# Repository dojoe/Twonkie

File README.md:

# Twonkie - a USB-PD sniffer based on Google's [Twinkie](https://www.chromium.org/chromium-os/developer-library/guides/hardware-schematics/twinkie/)

Twonkie is a USB-PD sniffer/injector/sink based on a Google project called Twinkie, re-engineered to be made in one-off quantities by mere mortals.

Twinkie is a great and pretty low-cost solution, and it's open-source so anyone could make their own, but unfortunately the Twinkie design uses a six-layer PCB and all BGA/wafer-scale parts - both of which are usually unavailable to the humble hobbyist.

So I designed the Twonkie, a slightly wonky sibling of Twinkie. It uses a four-layer PCB that can be manufactured cheaply by lots of services like OSHPark, and it makes a point to use only leaded parts for easier soldering (though the main microcontroller can optionally be QFN too via a dual footprint). The most difficult parts are likely the passives which are all 0402, and the USB-C connectors which are used in an unconventional way by misusing 90° upright connectors as 1.6mm straddle mounts (living up to the concept of being wonky).

## What does it look like?

Lookie here!

The PCB is exactly 1 inch squared, so $10 will get you three at OSHPark. In fact, let me take care of that for you:

<a href="https://oshpark.com/shared_projects/pj6N7ZkZ"></img></a>

_(Disclaimer: I am not affiliated with OSHPark, I just love their service to bits and they've been super helpful chaps time and time again.)_

The v1.0 and v2.0 Gerbers in this repo no longer need the botch wires around Q4 either, I'll update the photo as soon as I get the next board revision back.

## What's changed compared to the original Twinkie?

 * A bootloader button in addition to the USB_ID pin based bootloader selection.
 * Uses the INA237 part which supports the higher supply voltages of USB-PD Extended Power Range (EPR)
 * The microcontroller pins are rearranged for easier routing, so you'll need a different firmware. Binaries are provided and the firmware is easy to build from source.
 * The USB-C connectors are attached in a hair-raising straddle mount configuration. The way they're soldered to the PCB makes them rock solid though, maybe even more solid than the original Twinkie, and they transfer TB3 20Gbit/s lanes just fine.

## I see there's a v2.0 now - what's different?

The 2.0 version uses a different voltage/current monitor chip compared to Twonkie v1.0, the [INA237](ref/ina237.pdf), which supports higher bus voltages and therefore makes the Twonkie hardware ready for Extended Power Range (EPR). The INA260 used by Twonkie v1.0 (and the INA231 used by Twinkie) will take damage if subjected to the up to 48V specified by EPR.

## Sweet! How do I build my own?

I'm glad you asked! Get the board made via the OSH Park link above, or supply the v2.0 Gerbers in this repository to a PCB fab of your choice, get the parts from Digikey or Mouser or what have you, and follow the [Assembly instructions](hw/README.md) to build the device. I recommend ordering a few extra parts: Get one more of each Type-C connector since you're going to modify them in ways that might end up with a broken connector, and generously round up the number of 0402 passives since you're going to drop some of them and you will _never_ find them again :)

For the firmware, there are [Instructions for building and flashing](fw/README.md) in the [fw](fw) directory.

## None of the parts are available 😭 What do I do?

Here are some ideas about replacements for some parts that are most likely to be unavailable. None of these have been tested so you're on your own!

 * **INA237:** The INA237 is part of a device family and has two siblings with higher specs that TI claims are drop-in replacements: INA228 and INA238.
 * **STM32F072CB:** For one, the Twonkie has a dual footprint that will fit both the TQFP and QFN variants, i.e. the STM32F072CBT and STM32F072CBU. And if you are willing to sacrifice the PD sink functionaliy and only need the sniffer functionality you could also try the variants with 64k flash instead of 128k (STM32F072C8*) and only flash the first half of the firmware binary. Other device families than the F072 would require extensive firmware changes so I can't recommend that.
 * **USB-C plug / receptacle:** These might be a little trickier. Basically you need one that's meant for being mounted standing up on a board, has all USB-C pins wired out to L shaped pins and doesn't have any metal mounting prongs protruding into the board plane (or if it has you'll have to cut them off).

## I am a noob trying to solder and replicate the Twonkie. Got any beginner tips?

The KiCad schematic file contains the vendor part numbers and DigiKey order numbers for each part designator, and I exported the full list into a .csv file too - those are commonly called "Bill of materials" or BOM for short, and [this is the one for Twonkie 2.0](hw/v2.0/twonkie.bom.csv). You should be able to punch those part numbers into a parts supplier of your choice (I usually use [DigiKey](https://digikey.com/) but there are plenty others) to find the parts you need. If they have parts in stock they'll happily sell you small quantities, though at an increased price. Take care to order more of most parts than you need - especially the tiny passives (resistors, capacitors...) are easy to lose during assembly.

As for reading the schematic, it probably helps to have some familiarity with [USB-PD](https://www.usb.org/document-library/usb-power-delivery) and the [original project description](https://www.chromium.org/chromium-os/developer-library/guides/hardware-schematics/twinkie/), and then read up on the [device datasheets](ref/) to understand which part does what.

Having said all that, please be warned that the Twonkie is not exactly a noob project - unless you're already familiar with hand-soldering fine pitch SMT parts you may be in for a frustrating experience. Don't let that keep you from trying, but you should know what you're signing up for :)

# TODOs

 * [ ] Get Twinkie support upstreamed in sigrok/PulseView
 * [ ] v2.0 photos

# Similar projects

 * As luck would have it, [Greg Davill](https://github.com/gregdavill) started a project with the exact same goal at a very similar time, so there's now two of us :) https://github.com/gregdavill/PD-sniffer
 * [XenGi](https://github.com/XenGi) built a version of Twonkie v2.0 which uses a 0.8mm PCB and industry-standard straddle mount USB-C connectors. After [a bit of deliberation](https://github.com/dojoe/Twonkie/issues/10) I decided to stick with the 1.6mm PCB for stability and availability reasons but if you prefer a less haxxy way of attaching the connectors (and a 3D printed case!) feel free to check out his repo: https://gitlab.com/XenGi/Twonkie
   
# Licenses

## Hardware (as found in the `hw` subdirectory)

<p xmlns:cc="http://creativecommons.org/ns#" xmlns:dct="http://purl.org/dc/terms/">The hardware design of <a property="dct:title" rel="cc:attributionURL" href="https://github.com/dojoe/Twonkie">Twonkie</a> by <a rel="cc:attributionURL dct:creator" property="cc:attributionName" href="https://github.com/dojoe">Joachim "dojoe" Fenkes</a> is licensed under <a href="http://creativecommons.org/licenses/by/4.0/" target="_blank" rel="license noopener noreferrer" style="display:inline-block;">CC BY 4.0</a></p>

## Firmware (as found in the `fw` subdirectory)

The source code for the Twonkie's firmware is licensed under the 3-clause BSD license, see [its LICENSE file](fw/LICENSE).

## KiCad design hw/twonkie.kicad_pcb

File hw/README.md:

# Before you begin

## Recommended tools (apart from the usual)

The board is too tiny to stay put from its own weight so you'll need a proper vise. "Third Hand"s are no good for this since they can't clamp small boards properly and aren't stable enough. I recommend a StickVise or similar.

A knife with a straight, strong blade.

Non-serrated pliers.

You can solder everything using a smallish chisel tip and you'll be fine.
For enhanced comfort, a fine angled tip makes the passives much easier. I used a TS80-J02 with great success.

Gel flux. Liquid flux evaporates too quickly for my taste. I use Edsyn FL-22 for everything but there's plenty other good stuff out there too.

A watchmaker's loupe, more for inspection than for the actual soldering. Of all the tools I acquired last year, this super cheap 7x loupe made the biggest difference and it's never leaving my workbench again. Have a strong light (such as a phone camera LED) at the ready for inspection too, there's no such thing as "too much light".

## General tips

 * Keep both the schematics and the board file open while you build, you'll likely want to refer back to them more often than not.

 * I wholeheartedly recommend this thread by [@thingskatedid](https://twitter.com/thingskatedid): https://twitter.com/thingskatedid/status/1348234262886039558

 * **The passives are indistinguishable once taken out of their tapes!**
   * Always work with a single value at a time
   * Only remove as many components from the tape as you need right now
   * Immediately put the tape back into the pouch it came in, as that's where the value is noted - or write the value onto the tape.

 * For each group of passives below, it saves time to batch up different types of operations: First put a small solder blob on one pad of each site, then tack down each component, then solder the other side for all components in a row.

 * If the solder joints on nearby passives blob together a lot, use some flux and a little less solder. It's also a good idea to make a final flux pass across the finished passives just like you would be drag soldering a leaded part, it makes the solder joints look a lot nicer.

# Assembly instructions

These instructions are optimized for hand assembly; the components are grouped in a way that if you follow the groups in order you should never have one component in the way of soldering another. Within a given group the order does not matter; I recommend doing all components of one value before moving on to the next value.

The overall order of assembly is:
 1. Back side components
 2. Front side components
 3. Basic connectivity/bootloader test
 4. USB-C connectors

## Part 1: Back side

We start on the back side because that's where the STM32 sits which is the most daunting to solder, and because the components on that side are generally flatter so if you _have_ to solder without a vise they won't make the board as wobbly when you do the front side.

If your STM32 is a QFN part, take extra care to inspect its solder joints after you put it down. Once the board is fully populated any bad solder joints here will be hard to fix.

| Group | Components          | Value        |
|-------|---------------------|--------------|
| 1     | U4                  | STM32        |
| 2     | R3                  | 400          |
|       | R2, R5              | 620          |
| 3     | DS1                 | LED          |
| 4     | C3, C8              | 100n         |
|       | C7                  | 4.7µ         |
|       | C1                  | 1µ           |
|       | R4                  | 400          |
|       | FB1                 | Ferrite Bead |
| 5     | D1, U1, U3, Q4, R28 |              |

## Part 2: Front side

| Group | Components                 | Value         |
|-------|----------------------------|---------------|
| 6     | Q1, Q2, Q3                 | NFET          |
| 8     | R9, R17, R25, R26          | 4k75          |
|       | R10, R18                   | 1k            |
|       | R11, R19                   | 12k1          |
|       | R12, R20                   | 5k11          |
|       | R6, R7                     | 400           |
|       | R15, R23, R24              | 100           |
|       | R14, R22                   | 200           |
| 9     | R1, R8, R13, R16, R21, R27 | 35k7          |
| 10    | C2                         | 4u7           |
|       | C4, C9                     | 100n          |
|       | C5                         | 1u            |
|       | C6                         | 10n           |
| 11    | FB2                        | Ferrite Bead  |
| 12    | DS2, U5, U2, J3, SW1, R29  |               |

## Part 3: Basic connectivity / bootloader test

This step is done on the not-quite-finished Twonkie because if anything isn't right the board is much easier to hold in the vise without two USB-C connector sticking out.

1. Double check all components:
   * Are all ICs oriented the right way?
   * Did you miss any solder joints?
   * Do you see any obvious solder bridges?
2. Measure resistance between the 3V3 rail and GND, this is easiest at the output side of U3.
   Kiloohms are good, Ohms are an indication of a short somewhere.
3. Do the same on the input side of U3.
4. Hold down the bootloader switch and plug the dongle in via the Micro-B connector.
   It should now enumerate as the bootloader (VID 0x0483, PID 0xDF11, "STM32 BOOTLOADER")
5. Flash the firmware via the bootloader, then unplug and plug back in to boot the Twonkie firmware.
   * Check out the [Firmware README](../fw/README.md) for building and flashing instructions.
6. You can test the LED using the serial shell:
   * `tw sink` puts the device into sink mode where the firmware doesn't keep overwriting the LED state.
     You may need to reconnect the shell after this.
   * `gpioset LED_B_L 0` turns the blue LED on, `gpioset LED_B_L 1` turns it off.
   * Same for `LED_R_L` and `LED_G_L`
7. Check I2C connectivity to the two INA260 monitors:
   * `ina 0` attempts to access U1, `ina 1` does so for U2

That's all we can test for now, let's finish the board next.

## Part 4: USB-C connectors

The USB-C connectors are used in an unorthodox way: Straddle mount USB-C connectors for 1.6mm boards don't exist, so we take connectors meant for right-angle surface mounting and modify them into our own custom straddle mount configuration. With those modifications the solder connections work really well, and we achieve mechanical stability by soldering the connector shields to the board all around.

We start out with the unmodified connector. This is the receptacle but the steps for the plug are identical.

First, the mounting legs have to get out of the way. Grab them with your pliers and bend them back and forth until they break off.

Next up, the locating pegs have to go too. Cut them off close to the base.

Now comes the tricky part: We have to bend the pins of the connector slightly inwards so they touch the board edge at an angle, but not so much that they don't reach the board edge or break off. The photos should give you an idea of how far to bend them.

Start by sliding the knife under roughly a quarter to half the pins on one side, and gently bend them inwards. Bending only part of the pins at once requires less force and therefore allows for better control. Take care to **rotate** the knife blade around the long axis, as opposed to using it as a lever, so that all pins receive equal force and bend the same way.

Move along the row of pins, bending groups of pins inwards until the entire row is bent.

Repeat the same process on the other side; the end result should look something like this:

Now you can slide the connector into its place on the PCB. The PCB is designed such that the shell sits inside the PCB with a slight press fit. If you feel it's jammed in there too tightly you can simply sand off a little bit of the PCB, but sand off only very little and try to sand off both sides equally to maintain pin alignment.

Push the connector all the way towards the board edge and adjust its position until it sits exactly centered and in line with the board:

The pins on both sides should now align with the pads and touch the corner of the board edge. If there's a tiny gap that's no problem, the solder will bridge that. Larger gaps need to be fixed by adjusting the connector's position or bending the pins to compensate.

Once you're satisfied with the connector, tack down _one_ pin on one board side, double check that everything still looks good, then tack down _one_ pin on the opposite side. Triple check that everything still looks good, then you can drag solder all the pins into place.

When the pins have all been soldered, inspect them for missing connections or solder bridges and correct any that come up.

Finally you can solder down the shells: Using a soldering iron that can pump out a bit of heat (TS-80 is good, TS-100 is better, a powerful temperature controlled soldering station is best), first just pre-heat the shell for a bit, then add some solder and make sure it wets along the entire length of the neighboring pad. Then you can start heating the pad too and add loads of solder to make a solid connection. Do this on all four mounting pads and the connector won't go anywhere.

## Part 5: Enjoy!

And that's it! Clean your board with isopropanol and have fun with your new PD sniffer!

### Test 1: Sniff some power supply traffic

For starters, you can open a shell, type `tw trace on` and plug Twonkie in between a PD power supply and sink to watch them negotiate a power contract.

A very good test for many of the board devices is to do this in all four possible combinations of input and output plug orientation. The supply and sink should be able to negotiate a contract in all orientations, and Twonkie should be able to trace all of this. If some orientations don't work, check the solder joints on the USB-C connectors for bridges or opens - especially opens can be very sneaky with the haxxy edge mount we're using. If the connectors look alright, check the board devices next - especially the resistor banks and transistors are likely culprits since they directly interact with the USB-C control channels.

### Test 2: Twonkie as sink

The second test would be to attach only a power supply to Twonkie, with no sink at the other end, and type `tw sink` at the shell to put Twonkie into sink mode. (You may have to reconnect to the shell since Twonkie reboots into a different firmware.) Once in sink mode you can type `tw vbus` to watch what voltage the supply provides, and `pd 0 dev X` will limit the negotiated voltage to a maximum of `X` volts, so you can step through various supply voltages and watch them change. Test this in either plug orientation too; if you're having problems here you should double check the resistor banks on the control channels.

To go from sink mode back to sniffer mode you can type `reboot` at the shell.

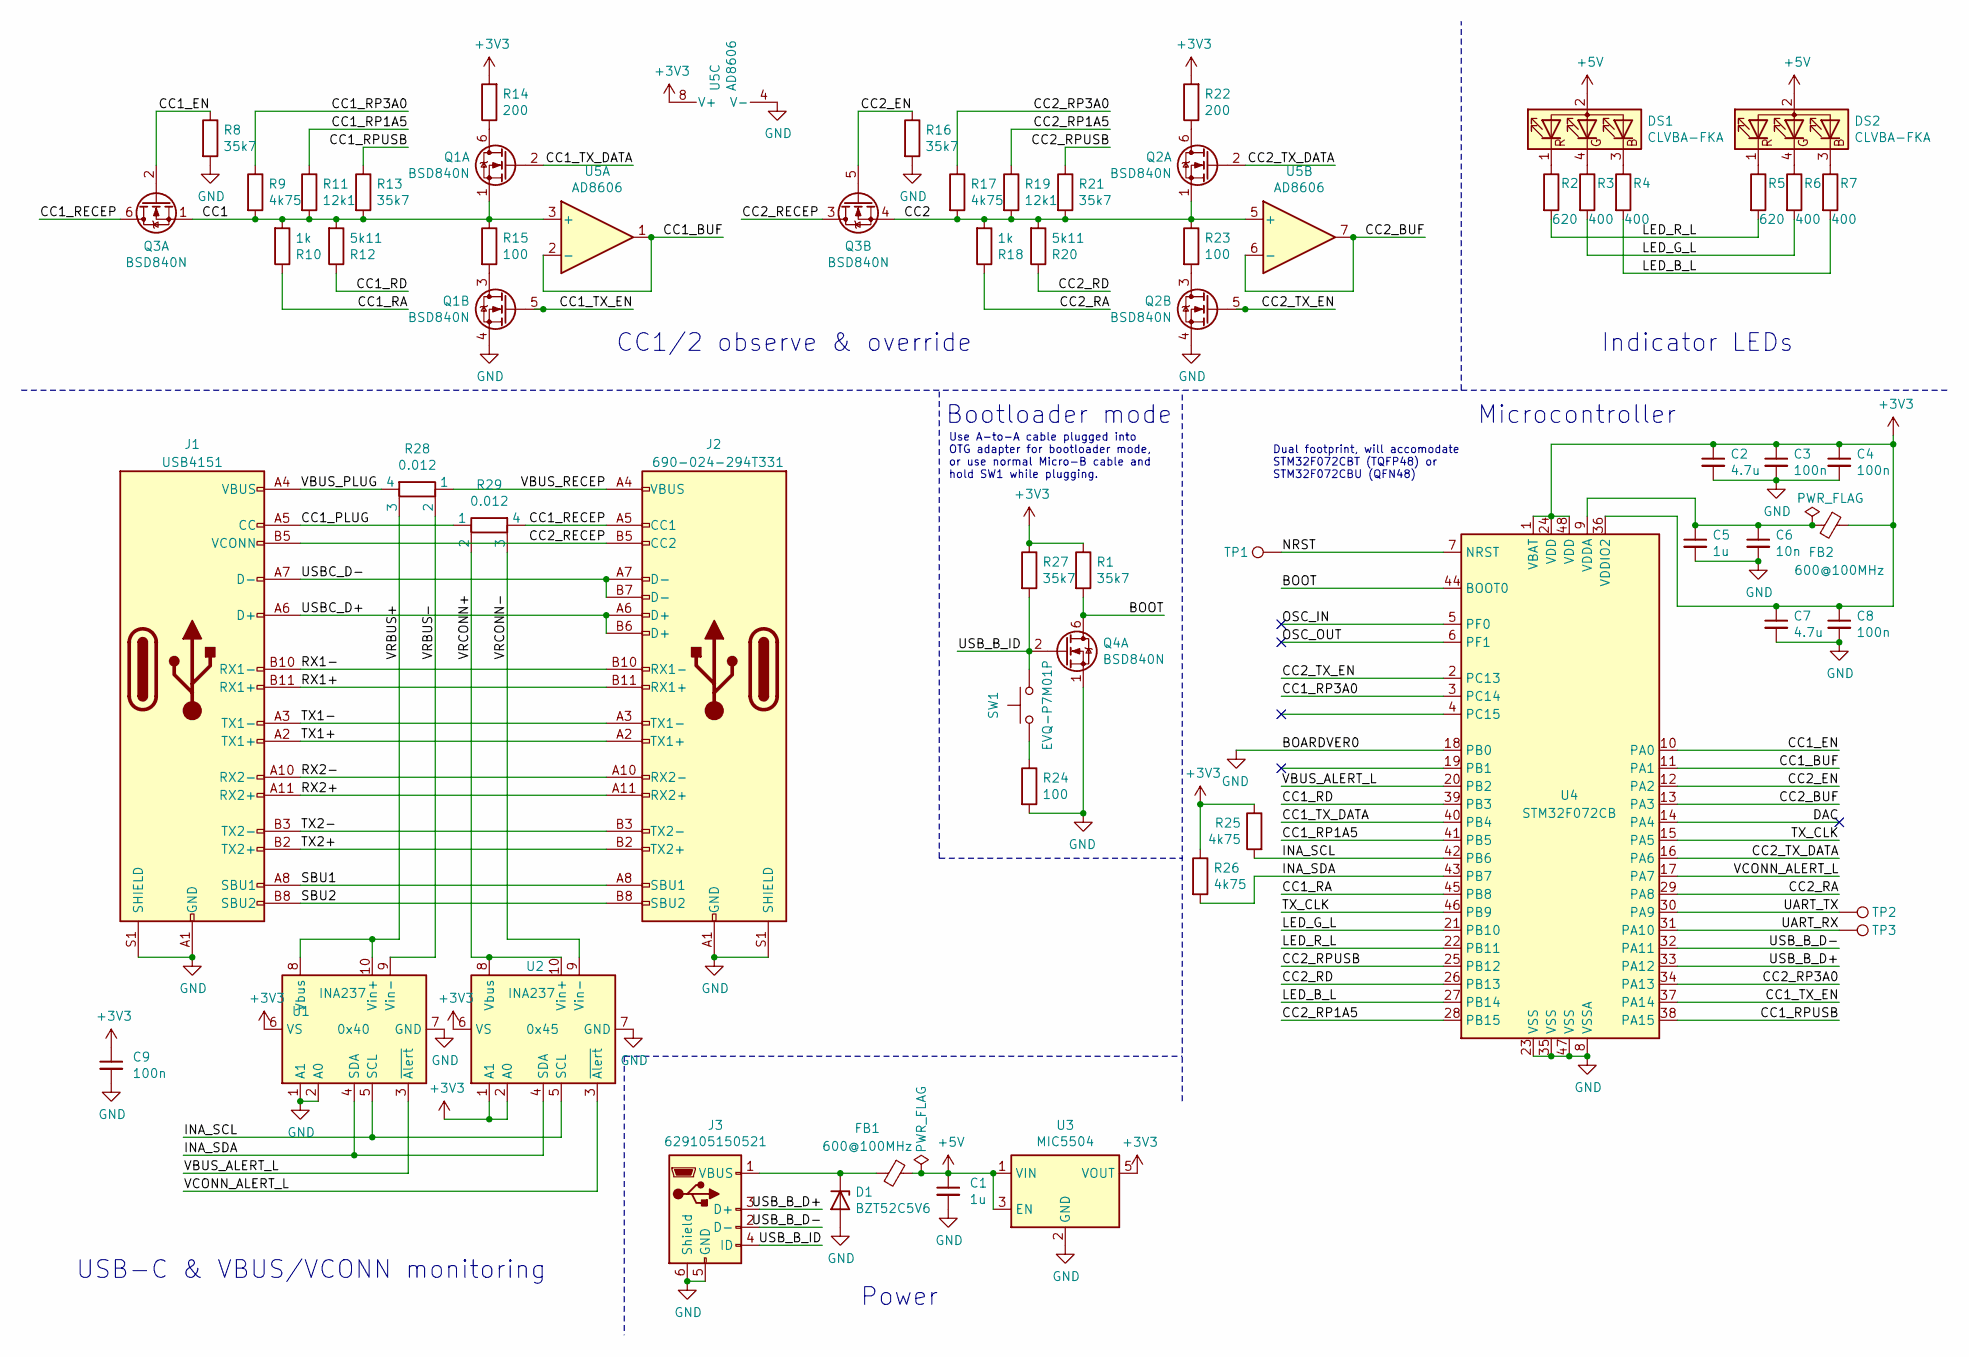
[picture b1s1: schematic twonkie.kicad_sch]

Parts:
C1, C5: 1u; C_0402_1005Metric_Pad0.74x0.62mm_HandSolder; Mfg P/N CL05A105MQ5NNNC; DigiKey P/N 1276-1235-1-ND
C2, C7: 4.7u; C_0402_1005Metric_Pad0.74x0.62mm_HandSolder; Mfg P/N CL05A475KQ5NRNC; DigiKey P/N 1276-1481-1-ND
C3, C4, C8, C9: 100n; C_0402_1005Metric_Pad0.74x0.62mm_HandSolder; Mfg P/N CL05B104KA5NNNC; DigiKey P/N 1276-6720-1-ND
C6: 10n; C_0402_1005Metric_Pad0.74x0.62mm_HandSolder; Mfg P/N CL05B103KB5NNNC; DigiKey P/N 1276-1028-1-ND
D1: BZT52C5V6; D_SOD-123; Mfg P/N BZT52C5V6-13-F; DigiKey P/N BZT52C5V6-13-FDICT-ND
DS1, DS2: CLVBA-FKA; LED_Cree-PLCC4_3.2x2.8mm_CCW; Mfg P/N CLVBA-FKA-CAEDH8BBB7A363; DigiKey P/N CLVBA-FKA-CAEDH8BBB7A363CT-ND
FB1, FB2: 600@100MHz; L_0402_1005Metric_Pad0.77x0.64mm_HandSolder; Mfg P/N BLM15AG601SN1D; DigiKey P/N 490-1006-1-ND
J1: USB4151; GCT_USB4151_EdgeMount; Mfg P/N USB4151-GF-C; DigiKey P/N 2073-USB4151-GF-CCT-ND
J2: 690-024-294T331; EDAC_690-024-294T331_EdgeMount; Mfg P/N USB4070-30-C; DigiKey P/N 2073-USB4070-30-CCT-ND
J3: 629105150521; USB_Micro-B_Wuerth_629105150521_HandSolder; Mfg P/N 629105150521; DigiKey P/N 732-5960-1-ND
Q1, Q2, Q3, Q4: BSD840N; SOT-363_SC-70-6; Mfg P/N BSD840NH6327XTSA1; DigiKey P/N BSD840NH6327XTSA1CT-ND
R1, R8, R13, R16, R21, R27: 35k7; R_0402_1005Metric_Pad0.72x0.64mm_HandSolder; Mfg P/N RC0402FR-0735K7L
R2, R5: 620; R_0402_1005Metric_Pad0.72x0.64mm_HandSolder; Mfg P/N RC0402FR-07620RL
R3, R4, R6, R7: 400; R_0402_1005Metric_Pad0.72x0.64mm_HandSolder; Mfg P/N RC0402FR-07402RL
R9, R17, R25, R26: 4k75; R_0402_1005Metric_Pad0.72x0.64mm_HandSolder; Mfg P/N RC0402FR-074K75L
R10, R18: 1k; R_0402_1005Metric_Pad0.72x0.64mm_HandSolder; Mfg P/N RC0402FR-071KL
R11, R19: 12k1; R_0402_1005Metric_Pad0.72x0.64mm_HandSolder; Mfg P/N RC0402FR-0712K1L
R12, R20: 5k11; R_0402_1005Metric_Pad0.72x0.64mm_HandSolder; Mfg P/N RC0402FR-075K11L
R14, R22: 200; R_0402_1005Metric_Pad0.72x0.64mm_HandSolder; Mfg P/N RC0402FR-07200RL
R15, R23, R24: 100; R_0402_1005Metric_Pad0.72x0.64mm_HandSolder; Mfg P/N RC0402FR-07100RL
R28, R29: 0.012; R_Shunt_Ohmite_LVK12; DigiKey P/N LVK12R012FERCT-ND
SW1: EVQ-P7M01P; SW_SPST_EVQP7C; Mfg P/N EVQ-P7M01P; DigiKey P/N P16770CT-ND
TP1, TP2, TP3: TestPoint; TestPoint_Pad_D1.0mm
U1, U2: INA237; VSSOP-10_3x3mm_P0.5mm; Mfg P/N INA237AIDGSR; DigiKey P/N 296-INA237AIDGSRCT-ND
U3: MIC5504; SOT-23-5_HandSoldering; Mfg P/N MIC5504-3.3YM5-TR; DigiKey P/N 576-4764-1-ND
U4: STM32F072CB; LQFP-48_7x7mm_P0.5mm-QFN48-Frankenstein; Mfg P/N STM32F072CBT; DigiKey P/N 497-18747-1-ND
U5: AD8606; MSOP-8_3x3mm_P0.65mm; Mfg P/N AD8606ARMZ-R7; DigiKey P/N 505-AD8606ARMZ-R7CT-ND

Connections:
+3V3: C2.1, C3.1, C4.1, C7.1, C8.1, C9.1, FB2.1, R1.1, R14.2, R22.2, R25.1, R26.1, R27.1, U1.6 (VS), U2.1 (A1), U2.2 (A0), U2.6 (VS), U3.5 (VOUT), U4.1 (VBAT), U4.24 (VDD), U4.36 (VDDIO2), U4.48 (VDD), U5.8 (V+)
+5V: C1.1, DS1.2 (A), DS2.2 (A), FB1.1, U3.1 (VIN), U3.3 (EN)
/BOOT: Q4.6 (D), R1.2, U4.44 (BOOT0)
/CC1: Q1.1 (S), Q3.1 (S), R9.2, R10.2, R11.2, R12.2, R13.2, R15.1, U5.3 (+)
/CC1_BUF: U4.11 (PA1), U5.1, U5.2 (-)
/CC1_EN: Q3.2 (G), R8.1, U4.10 (PA0)
/CC1_PLUG: J1.A5 (CC), R29.1
/CC1_RA: R10.1, U4.45 (PB8)
/CC1_RD: R12.1, U4.39 (PB3)
/CC1_RECEP: J2.A5 (CC1), Q3.6 (D), R29.4
/CC1_RP1A5: R11.1, U4.41 (PB5)
/CC1_RP3A0: R9.1, U4.3 (PC14)
/CC1_RPUSB: R13.1, U4.38 (PA15)
/CC1_TX_DATA: Q1.2 (G), U4.40 (PB4)
/CC1_TX_EN: Q1.5 (G), U4.37 (PA14)
/CC2: Q2.1 (S), Q3.4 (S), R17.2, R18.2, R19.2, R20.2, R21.2, R23.1, U5.5 (+)
/CC2_BUF: U4.13 (PA3), U5.6 (-), U5.7
/CC2_EN: Q3.5 (G), R16.1, U4.12 (PA2)
/CC2_RA: R18.1, U4.29 (PA8)
/CC2_RD: R20.1, U4.26 (PB13)
/CC2_RECEP: J1.B5 (VCONN), J2.B5 (CC2), Q3.3 (D)
/CC2_RP1A5: R19.1, U4.28 (PB15)
/CC2_RP3A0: R17.1, U4.34 (PA13)
/CC2_RPUSB: R21.1, U4.25 (PB12)
/CC2_TX_DATA: Q2.2 (G), U4.16 (PA6)
/CC2_TX_EN: Q2.5 (G), U4.2 (PC13)
/DAC: U4.14 (PA4)
/INA_SCL: R25.2, U1.5 (SCL), U2.5 (SCL), U4.42 (PB6)
/INA_SDA: R26.2, U1.4 (SDA), U2.4 (SDA), U4.43 (PB7)
/LED_B_L: R4.2, R7.2, U4.27 (PB14)
/LED_G_L: R3.2, R6.2, U4.21 (PB10)
/LED_R_L: R2.2, R5.2, U4.22 (PB11)
/NRST: TP1.1, U4.7 (NRST)
/OSC_IN: U4.5 (PF0)
/OSC_OUT: U4.6 (PF1)
/RX1+: J1.B11 (RX1+), J2.B11 (RX1+)
/RX1-: J1.B10 (RX1-), J2.B10 (RX1-)
/RX2+: J1.A11 (RX2+), J2.A11 (RX2+)
/RX2-: J1.A10 (RX2-), J2.A10 (RX2-)
/SBU1: J1.A8 (SBU1), J2.A8 (SBU1)
/SBU2: J1.B8 (SBU2), J2.B8 (SBU2)
/TX1+: J1.A2 (TX1+), J2.A2 (TX1+)
/TX1-: J1.A3 (TX1-), J2.A3 (TX1-)
/TX2+: J1.B2 (TX2+), J2.B2 (TX2+)
/TX2-: J1.B3 (TX2-), J2.B3 (TX2-)
/TX_CLK: U4.15 (PA5), U4.46 (PB9)
/UART_RX: TP3.1, U4.31 (PA10)
/UART_TX: TP2.1, U4.30 (PA9)
/USBC_D+: J1.A6 (D+), J2.A6 (D+), J2.B6 (D+)
/USBC_D-: J1.A7 (D-), J2.A7 (D-), J2.B7 (D-)
/USB_B_D+: J3.3 (D+), U4.33 (PA12)
/USB_B_D-: J3.2 (D-), U4.32 (PA11)
/USB_B_ID: J3.4 (ID), Q4.2 (G), R27.2, SW1.1
/VBUS_ALERT_L: U1.3 (~Alert), U4.20 (PB2)
/VBUS_PLUG: J1.A4 (VBUS), J1.A9 (VBUS), J1.B4 (VBUS), J1.B9 (VBUS), R28.4
/VBUS_RECEP: J2.A4 (VBUS), J2.A9 (VBUS), J2.B4 (VBUS), J2.B9 (VBUS), R28.1
/VCONN_ALERT_L: U2.3 (~Alert), U4.17 (PA7)
/VRBUS+: R28.3, U1.8 (Vbus), U1.10 (Vin+)
/VRBUS-: R28.2, U1.9 (Vin-)
/VRCONN+: R29.2, U2.8 (Vbus), U2.10 (Vin+)
/VRCONN-: R29.3, U2.9 (Vin-)
GND: C1.2, C2.2, C3.2, C4.2, C5.2, C6.2, C7.2, C8.2, C9.2, D1.2 (A), J1.A1 (GND), J1.A12 (GND), J1.B1 (GND), J1.B12 (GND), J1.S1 (SHIELD), J1.S2 (SHIELD), J1.S3 (SHIELD), J1.S4 (SHIELD), J1.S5 (SHIELD), J1.S6 (SHIELD), J2.A1 (GND), J2.A12 (GND), J2.B1 (GND), J2.B12 (GND), J2.S1 (SHIELD), J2.S2 (SHIELD), J2.S3 (SHIELD), J2.S4 (SHIELD), J2.S5 (SHIELD), J2.S6 (SHIELD), J2.S7 (SHIELD), J2.S8 (SHIELD), J3.5 (GND), J3.6 (Shield), Q1.4 (S), Q2.4 (S), Q4.1 (S), R8.2, R16.2, R24.2, U1.1 (A1), U1.2 (A0), U1.7 (GND), U2.7 (GND), U3.2 (GND), U4.8 (VSSA), U4.18 (PB0), U4.23 (VSS), U4.35 (VSS), U4.47 (VSS), U5.4 (V-)
unnamed: C5.1, C6.1, FB2.2, U4.9 (VDDA)
unnamed: D1.1 (K), FB1.2, J3.1 (VBUS)
unnamed: DS1.1 (RK), R2.1
unnamed: DS1.3 (BK), R4.1
unnamed: DS1.4 (GK), R3.1
unnamed: DS2.1 (RK), R5.1
unnamed: DS2.3 (BK), R7.1
unnamed: DS2.4 (GK), R6.1
unnamed: Q1.3 (D), R15.2
unnamed: Q1.6 (D), R14.1
unnamed: Q2.3 (D), R23.2
unnamed: Q2.6 (D), R22.1
unnamed: R24.1, SW1.2

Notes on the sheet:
Use A-to-A cable plugged into OTG adapter for bootloader mode, or use normal Micro-B cable and hold SW1 while plugging.
Dual footprint, will accomodate STM32F072CBT (TQFP48) or STM32F072CBU (QFN48)
Bootloader mode
Indicator LEDs
Power
CC1/2 observe & override
Microcontroller
USB-C & VBUS/VCONN monitoring

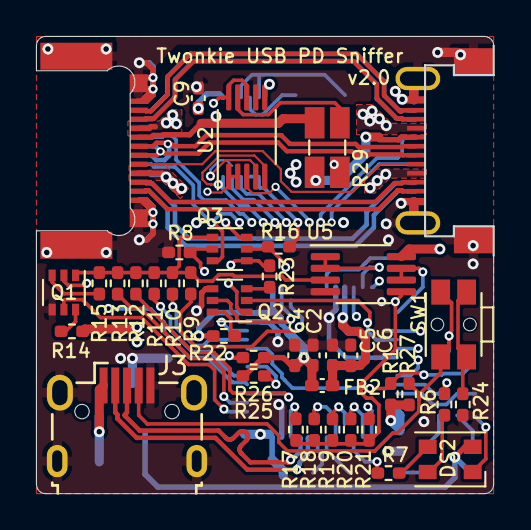
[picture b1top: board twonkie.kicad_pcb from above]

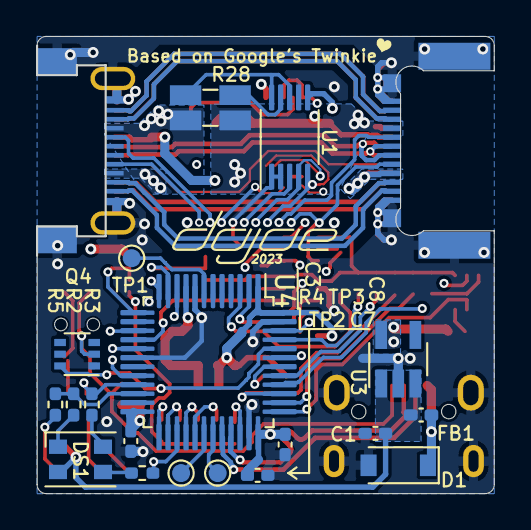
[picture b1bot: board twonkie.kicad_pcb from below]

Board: 4 copper layers, 25.4 x 25.4 mm, 62 parts (20 on the bottom side), 72 nets.

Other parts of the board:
HEART: (no value)
OSHW_LOGO: oshw_logo_silkscreen_back_3.5mm
dojoe-logo: G***; dojoe-logo

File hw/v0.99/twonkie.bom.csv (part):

"Source:","D:\Projects\Twonkie\hw\twonkie.sch"
"Date:","18/11/2020 22:25:42"
"Tool:","Eeschema (5.1.7)-1"
"Generator:","C:\Progs\Dev\KiCad\bin\scripting\plugins/bom_csv_grouped_by_value.py"
"Component Count:","50"

"Individual Components:"

"Item","Qty","Reference(s)","Value","LibPart","Footprint","Datasheet","DigiKey P/N","I2C addr","Manufacturer","Mfg P/N"
"","","C1","1u","Device:C","Capacitor_SMD:C_0402_1005Metric_Pad0.74x0.62mm_HandSolder","~","1276-1235-1-ND","","Samsung Electro-Mechanics","CL05A105MQ5NNNC"
"","","C2","4.7u","Device:C_Small","Capacitor_SMD:C_0402_1005Metric_Pad0.74x0.62mm_HandSolder","~","1276-1481-1-ND","","Samsung Electro-Mechanics","CL05A475KQ5NRNC"
"","","C3","100n","Device:C_Small","Capacitor_SMD:C_0402_1005Metric_Pad0.74x0.62mm_HandSolder","~","1276-6720-1-ND","","Samsung Electro-Mechanics","CL05B104KA5NNNC"
"","","C4","100n","Device:C_Small","Capacitor_SMD:C_0402_1005Metric_Pad0.74x0.62mm_HandSolder","~","1276-6720-1-ND","","Samsung Electro-Mechanics","CL05B104KA5NNNC"
"","","C5","1u","Device:C_Small","Capacitor_SMD:C_0402_1005Metric_Pad0.74x0.62mm_HandSolder","~","1276-1235-1-ND","","Samsung Electro-Mechanics","CL05A105MQ5NNNC"
"","","C6","10n","Device:C_Small","Capacitor_SMD:C_0402_1005Metric_Pad0.74x0.62mm_HandSolder","~","1276-1028-1-ND","","Samsung Electro-Mechanics","CL05B103KB5NNNC"
"","","C7","4.7u","Device:C_Small","Capacitor_SMD:C_0402_1005Metric_Pad0.74x0.62mm_HandSolder","~","1276-1481-1-ND","","Samsung Electro-Mechanics","CL05A475KQ5NRNC"
"","","C8","100n","Device:C_Small","Capacitor_SMD:C_0402_1005Metric_Pad0.74x0.62mm_HandSolder","~","1276-6720-1-ND","","Samsung Electro-Mechanics","CL05B104KA5NNNC"
"","","C9","100n","Device:C","Capacitor_SMD:C_0402_1005Metric_Pad0.74x0.62mm_HandSolder","~","1276-6720-1-ND","","Samsung Electro-Mechanics","CL05B104KA5NNNC"
"","","D1","BZT52C5V6","Diode:BZT52Bxx","Diode_SMD:D_SOD-123","https://diotec.com/tl_files/diotec/files/pdf/datasheets/bzt5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","BZT52C5V6-13-FDICT-ND","","Diodes Inc.","BZT52C5V6-13-F"
"","","DS1","CLVBA-FKA","Device:LED_RABG","LED_SMD:LED_Cree-PLCC4_3.2x2.8mm_CCW","~","CLVBA-FKA-CAEDH8BBB7A363CT-ND","","Cree","CLVBA-FKA-CAEDH8BBB7A363"
"","","DS2","CLVBA-FKA","Device:LED_RABG","LED_SMD:LED_Cree-PLCC4_3.2x2.8mm_CCW","~","CLVBA-FKA-CAEDH8BBB7A363CT-ND","","Cree","CLVBA-FKA-CAEDH8BBB7A363"
"","","FB1","600@100MHz","Device:Ferrite_Bead_Small","Inductor_SMD:L_0402_1005Metric_Pad0.77x0.64mm_HandSolder","~","490-1006-1-ND","","MuRata","BLM15AG601SN1D"
"","","FB2","600@100MHz","Device:Ferrite_Bead_Small","Inductor_SMD:L_0402_1005Metric_Pad0.77x0.64mm_HandSolder","~","490-1006-1-ND","","MuRata","BLM15AG601SN1D"
"","","J1","USB4151","twonkie:USB_C_Plug","twonkie:GCT_USB4151_EdgeMount","https://www.usb.org/sites/default/files/documents/usb_type-c.zip","2073-USB4151-GF-CCT-ND","","GCT","USB4151-GF-C"
"","","J2","690-024-294T331","twonkie:USB_C_Receptacle","twonkie:EDAC_690-024-294T331_EdgeMount","https://www.usb.org/sites/default/files/documents/usb_type-c.zip","151-1601-1-ND","","EDAC","690-024-294T331"
"","","J3","629105150521","Connector:USB_B_Micro","Connector_USB:USB_Micro-B_Wuerth_629105150521_CircularHoles","~","732-5960-1-ND","","Würth","629105150521"
"","","Q1","BSD840N","Transistor_FET:FDG6335N","Package_TO_SOT_SMD:SOT-363_SC-70-6","http://www.gneic.com/product/datasheet/FDG6335N-1122853.pdf","BSD840NH6327XTSA1CT-ND","","Infineon","BSD840NH6327XTSA1"
"","","Q2","BSD840N","Transistor_FET:FDG6335N","Package_TO_SOT_SMD:SOT-363_SC-70-6","http://www.gneic.com/product/datasheet/FDG6335N-1122853.pdf","BSD840NH6327XTSA1CT-ND","","Infineon","BSD840NH6327XTSA1"
"","","Q3","BSD840N","Transistor_FET:FDG6335N","Package_TO_SOT_SMD:SOT-363_SC-70-6","http://www.gneic.com/product/datasheet/FDG6335N-1122853.pdf","BSD840NH6327XTSA1CT-ND","","Infineon","BSD840NH6327XTSA1"
"","","R1","35k7","Device:R","Resistor_SMD:R_0402_1005Metric_Pad0.72x0.64mm_HandSolder","~","311-35.7KLRCT-ND","","Yageo","RC0402FR-0735K7L"
"","","R2","390","Device:R","Resistor_SMD:R_0402_1005Metric_Pad0.72x0.64mm_HandSolder","~","YAG3239CT-ND","","Yageo","RC0402FR-07806RL"
"","","R3","240","Device:R","Resistor_SMD:R_0402_1005Metric_Pad0.72x0.64mm_HandSolder","~","","","Yageo","RC0402FR-07240RL"
"","","R4","240","Device:R","Resistor_SMD:R_0402_1005Metric_Pad0.72x0.64mm_HandSolder","~","","","Yageo","RC0402FR-07240RL"
"","","R5","390","Device:R","Resistor_SMD:R_0402_1005Metric_Pad0.72x0.64mm_HandSolder","~","YAG3239CT-ND","","Yageo","RC0402FR-07806RL"
"","","R6","240","Device:R","Resistor_SMD:R_0402_1005Metric_Pad0.72x0.64mm_HandSolder","~","","","Yageo","RC0402FR-07240RL"
"","","R7","240","Device:R","Resistor_SMD:R_0402_1005Metric_Pad0.72x0.64mm_HandSolder","~","","","Yageo","RC0402FR-07240RL"
"","","R8","35k7","Device:R","Resistor_SMD:R_0402_1005Metric_Pad0.72x0.64mm_HandSolder","~","311-35.7KLRCT-ND","","Yageo","RC0402FR-0735K7L"
"","","R9","4k75","Device:R","Resistor_SMD:R_0402_1005Metric_Pad0.72x0.64mm_HandSolder","~","311-4.75KLCT-ND","","Yageo","RC0402FR-074K75L"
"","","R10","1k","Device:R","Resistor_SMD:R_0402_1005Metric_Pad0.72x0.64mm_HandSolder","~","","","Yageo","RC0402FR-071KL"
"","","R11","12k1","Device:R","Resistor_SMD:R_0402_1005Metric_Pad0.72x0.64mm_HandSolder","~","","","Yageo","RC0402FR-0712K1L"
"","","R12","5k11","Device:R","Resistor_SMD:R_0402_1005Metric_Pad0.72x0.64mm_HandSolder","~","","","Yageo","RC0402FR-075K11L"
"","","R13","35k7","Device:R","Resistor_SMD:R_0402_1005Metric_Pad0.72x0.64mm_HandSolder","~","311-35.7KLRCT-ND","","Yageo","RC0402FR-0735K7L"
"","","R14","200","Device:R","Resistor_SMD:R_0402_1005Metric_Pad0.72x0.64mm_HandSolder","~","","","Yageo","RC0402FR-07200RL"
"","","R15","100","Device:R","Resistor_SMD:R_0402_1005Metric_Pad0.72x0.64mm_HandSolder","~","","","Yageo","RC0402FR-07100RL"
"","","R16","35k7","Device:R","Resistor_SMD:R_0402_1005Metric_Pad0.72x0.64mm_HandSolder","~","311-35.7KLRCT-ND","","Yageo","RC0402FR-0735K7L"
"","","R17","4k75","Device:R","Resistor_SMD:R_0402_1005Metric_Pad0.72x0.64mm_HandSolder","~","311-4.75KLCT-ND","","Yageo","RC0402FR-074K75L"
"","","R18","1k","Device:R","Resistor_SMD:R_0402_1005Metric_Pad0.72x0.64mm_HandSolder","~","","","Yageo","RC0402FR-071KL"
"","","R19","12k1","Device:R","Resistor_SMD:R_0402_1005Metric_Pad0.72x0.64mm_HandSolder","~","","","Yageo","RC0402FR-0712K1L"
"","","R20","5k11","Device:R","Resistor_SMD:R_0402_1005Metric_Pad0.72x0.64mm_HandSolder","~","","","Yageo","RC0402FR-075K11L"
"","","R21","35k7","Device:R","Resistor_SMD:R_0402_1005Metric_Pad0.72x0.64mm_HandSolder","~","311-35.7KLRCT-ND","","Yageo","RC0402FR-0735K7L"
"","","R22","200","Device:R","Resistor_SMD:R_0402_1005Metric_Pad0.72x0.64mm_HandSolder","~","","","Yageo","RC0402FR-07200RL"
"","","R23","100","Device:R","Resistor_SMD:R_0402_1005Metric_Pad0.72x0.64mm_HandSolder","~","","","Yageo","RC0402FR-07100RL"
"","","R24","100","Device:R","Resistor_SMD:R_0402_1005Metric_Pad0.72x0.64mm_HandSolder","~","","","Yageo","RC0402FR-07100RL"
"","","SW1","EVQ-P7M01P","Switch:SW_Push","Button_Switch_SMD:SW_SPST_EVQP7C","http://www.apem.com/int/index.php?controller=attachment&id_a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","P16770CT-ND","","Panasonic","EVQ-P7M01P"
"","","U1","INA260","Sensor:INA260","Package_SO:TSSOP-16_4.4x5mm_P0.65mm","https://www.analog.com/media/en/technical-documentation/data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","296-47777-1-ND","0x40","TI","INA260AIPWR"
"","","U2","INA260","Sensor:INA260","Package_SO:TSSOP-16_4.4x5mm_P0.65mm","https://www.analog.com/media/en/technical-documentation/data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","296-47777-1-ND","0x41","TI","INA260AIPWR"
"","","U3","MIC5504","Regulator_Linear:MIC5504-3.3YM5","Package_TO_SOT_SMD:SOT-23-5_HandSoldering","https://www.analog.com/media/en/technical-documentation/data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","576-4764-1-ND","","Microchip","MIC5504-3.3YM5-TR"
"","","U4","STM32F072CB","MCU_ST_STM32F0:STM32F042C6Tx","Package_QFP:LQFP-48_7x7mm_P0.5mm","https://www.analog.com/media/en/technical-documentation/data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","497-19319-1-ND","","STMicro","STM32F042C6T6TR"
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
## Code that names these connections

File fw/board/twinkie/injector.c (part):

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	} cfgs[2];
} res_cfg[] = {
	[INJ_RES_NONE]  = {"NONE"},
	[INJ_RES_RA]    = {"RA", {{GPIO_CC1_RA, GPIO_ODR_LOW},
				  {GPIO_CC2_RA, GPIO_ODR_LOW} } },
	[INJ_RES_RD]    = {"RD", {{GPIO_CC1_RD, GPIO_ODR_LOW},
				  {GPIO_CC2_RD, GPIO_ODR_LOW} } },
	[INJ_RES_RPUSB] = {"RPUSB", {{GPIO_CC1_RPUSB, GPIO_OUT_HIGH},
				     {GPIO_CC2_RPUSB, GPIO_OUT_HIGH} } },
	[INJ_RES_RP1A5] = {"RP1A5", {{GPIO_CC1_RP1A5, GPIO_OUT_HIGH},
				     {GPIO_CC2_RP1A5, GPIO_OUT_HIGH} } },
	[INJ_RES_RP3A0] = {"RP3A0", {{GPIO_CC1_RP3A0, GPIO_OUT_HIGH},
				     {GPIO_CC2_RP3A0, GPIO_OUT_HIGH} } },
};

#define CC_RA(cc)  (cc < PD_SRC_RD_THRESHOLD)
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
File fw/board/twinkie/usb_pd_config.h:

/* Copyright (c) 2014 The Chromium OS Authors. All rights reserved.
 * Use of this source code is governed by a BSD-style license that can be
 * found in the LICENSE file.
 */

/* USB Power delivery board configuration */

#ifndef __CROS_EC_USB_PD_CONFIG_H
#define __CROS_EC_USB_PD_CONFIG_H

#include "ina2xx.h"

/* Timer selection for baseband PD communication */
#define TIM_CLOCK_PD_TX_C0 17
#define TIM_CLOCK_PD_RX_C0 1

#define TIM_CLOCK_PD_TX(p) TIM_CLOCK_PD_TX_C0
#define TIM_CLOCK_PD_RX(p) TIM_CLOCK_PD_RX_C0

/* TX and RX timer register */
#define TIM_REG_TX_C0 (STM32_TIM_BASE(TIM_CLOCK_PD_TX_C0))
#define TIM_REG_RX_C0 (STM32_TIM_BASE(TIM_CLOCK_PD_RX_C0))
#define TIM_REG_TX(p) TIM_REG_TX_C0
#define TIM_REG_RX(p) TIM_REG_RX_C0

/* Timer channel */
#define TIM_RX_CCR_C0 1
#define TIM_TX_CCR_C0 1

/* RX timer capture/compare register */
#define TIM_CCR_C0 (&STM32_TIM_CCRx(TIM_CLOCK_PD_RX_C0, TIM_RX_CCR_C0))
#define TIM_RX_CCR_REG(p) TIM_CCR_C0

/* use the hardware accelerator for CRC */
#define CONFIG_HW_CRC

/* TX is using SPI1 on PA6/PB4 */
#define SPI_REGS(p) STM32_SPI1_REGS
#define DMAC_SPI_TX(p) STM32_DMAC_CH3

static inline void spi_enable_clock(int port)
{
	STM32_RCC_APB2ENR |= STM32_RCC_PB2_SPI1;
}

/* RX is using COMP1 or COMp2 triggering TIM1 CH1  */
#define CMP1OUTSEL STM32_COMP_CMP1OUTSEL_TIM1_IC1
#define CMP2OUTSEL STM32_COMP_CMP2OUTSEL_TIM1_IC1

#define DMAC_TIM_RX(p) STM32_DMAC_CH2
#define TIM_RX_CCR_IDX(p) TIM_RX_CCR_C0
#define TIM_TX_CCR_IDX(p) TIM_TX_CCR_C0
#define TIM_CCR_CS  1
#define EXTI_COMP_MASK(p) ((1 << 21) | (1 << 22))
#define IRQ_COMP STM32_IRQ_COMP
/* triggers packet detection on comparator falling edge */
#define EXTI_XTSR STM32_EXTI_FTSR

/* the pins used for communication need to be hi-speed */
static inline void pd_set_pins_speed(int port)
{
	/* 40 MHz pin speed on SPI TX PB4 */
	STM32_GPIO_OSPEEDR(GPIO_B) |= 0x00000300;
	/* 40 MHz pin speed on SPI TX PA6 */
	STM32_GPIO_OSPEEDR(GPIO_A) |= 0x00003000;
	/* 40 MHz pin speed on TIM17_CH1 (PB9) */
	STM32_GPIO_OSPEEDR(GPIO_B) |= 0x000C0000;
}

/* Reset SPI peripheral used for TX */
static inline void pd_tx_spi_reset(int port)
{
	/* Reset SPI1 */
	STM32_RCC_APB2RSTR |= (1 << 12);
	STM32_RCC_APB2RSTR &= ~(1 << 12);
}

/* Drive the CC line from the TX block */
static inline void pd_tx_enable(int port, int polarity)
{
#if 0 /* Transmit only on the active CC line */
	if (polarity) {
		gpio_set_level(GPIO_CC2_TX_EN, 1);
		/* TX_DATA on PA6 is now connected to SPI1 */
		gpio_set_alternate_function(GPIO_A, 0x0040, 0);
	} else {
		gpio_set_level(GPIO_CC1_TX_EN, 1);
		/* TX_DATA on PB4 is now connected to SPI1 */
		gpio_set_alternate_function(GPIO_B, 0x0010, 0);
	}
#else /* Transmit on both CC lines */
	gpio_set_level(GPIO_CC2_TX_EN, 1);
	gpio_set_level(GPIO_CC1_TX_EN, 1);
	/* TX_DATA on PA6 is now connected to SPI1 */
	gpio_set_alternate_function(GPIO_A, 0x0040, 0);
	/* TX_DATA on PB4 is now connected to SPI1 */
	gpio_set_alternate_function(GPIO_B, 0x0010, 0);
#endif
}

/* Put the TX driver in Hi-Z state */
static inline void pd_tx_disable(int port, int polarity)
{
	/* TX_DATA on PB4 is an output low GPIO to disable the FET */
	STM32_GPIO_MODER(GPIO_B) = (STM32_GPIO_MODER(GPIO_B) & ~(3 << (2*4)))
							     |  (1 << (2*4));
	/* TX_DATA on PA6 is an output low GPIO to disable the FET */
	STM32_GPIO_MODER(GPIO_A) = (STM32_GPIO_MODER(GPIO_A) & ~(3 << (2*6)))
							     |  (1 << (2*6));
	/*
	 * Tri-state the low side after the high side
	 * to ensure we are not going above Vnc
	 */
	gpio_set_level(GPIO_CC1_TX_EN, 0);
	gpio_set_level(GPIO_CC2_TX_EN, 0);
}

/* we know the plug polarity, do the right configuration */
static inline void pd_select_polarity(int port, int polarity)
{
	/* use the right comparator */
	STM32_COMP_CSR = (STM32_COMP_CSR
		& ~(STM32_COMP_CMP1INSEL_MASK | STM32_COMP_CMP2INSEL_MASK
		  |STM32_COMP_CMP1EN | STM32_COMP_CMP2EN))
		| STM32_COMP_CMP1INSEL_INM4 | STM32_COMP_CMP2INSEL_INM4
		| (polarity ? STM32_COMP_CMP2EN : STM32_COMP_CMP1EN);
}

/* Initialize pins used for clocking */
static inline void pd_tx_init(void)
{
	gpio_config_module(MODULE_USB_PD, 1);

#ifndef CONFIG_USB_PD_TX_PHY_ONLY
	/* Detect when VBUS crosses the 4.5V threshold (1.25mV/bit) */
	ina2xx_set_vbus_ov_limit(0, INA2XX_MV_BUS(4500));
	/* start as a power consumer */
	gpio_set_level(GPIO_CC1_RD, 0);
	gpio_set_level(GPIO_CC2_RD, 0);
#endif /* CONFIG_USB_PD_TX_PHY_ONLY */
}

static inline void pd_set_host_mode(int port, int enable)
{
	if (enable) {
		gpio_set_level(GPIO_CC1_RD, 1);
		gpio_set_level(GPIO_CC2_RD, 1);
		/* set Rp by driving high RPUSB GPIO */
		gpio_set_flags(GPIO_CC1_RPUSB, GPIO_OUT_HIGH);
		gpio_set_flags(GPIO_CC2_RPUSB, GPIO_OUT_HIGH);
	} else {
		/* put back RPUSB GPIO in the default state and set Rd */
		gpio_set_flags(GPIO_CC1_RPUSB, GPIO_ODR_HIGH);
		gpio_set_flags(GPIO_CC2_RPUSB, GPIO_ODR_HIGH);
		gpio_set_level(GPIO_CC1_RD, 0);
		gpio_set_level(GPIO_CC2_RD, 0);
	}
}

static inline void pd_config_init(int port, uint8_t power_role)
{
#ifndef CONFIG_USB_PD_TX_PHY_ONLY
	/* Set CC pull resistors */
	pd_set_host_mode(port, power_role);
#endif /* CONFIG_USB_PD_TX_PHY_ONLY */

	/* Initialize TX pins and put them in Hi-Z */
	pd_tx_init();
}

static inline int pd_adc_read(int port, int cc)
{
	if (cc == 0)
		return adc_read_channel(ADC_CH_CC1_PD);
	else
		return adc_read_channel(ADC_CH_CC2_PD);
}

#endif /* __CROS_EC_USB_PD_CONFIG_H */

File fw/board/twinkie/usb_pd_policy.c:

/* Copyright (c) 2014 The Chromium OS Authors. All rights reserved.
 * Use of this source code is governed by a BSD-style license that can be
 * found in the LICENSE file.
 */

#include "common.h"
#include "config.h"
#include "console.h"
#include "gpio.h"
#include "hooks.h"
#include "registers.h"
#include "task.h"
#include "timer.h"
#include "util.h"
#include "usb_pd.h"

#define CPRINTF(format, args...) cprintf(CC_USBPD, format, ## args)
#define CPRINTS(format, args...) cprints(CC_USBPD, format, ## args)

#define PDO_FIXED_FLAGS (PDO_FIXED_EXTERNAL | PDO_FIXED_DATA_SWAP)

const uint32_t pd_src_pdo[] = {
		PDO_FIXED(5000,  3000, PDO_FIXED_FLAGS),
		PDO_FIXED(12000, 3000, PDO_FIXED_FLAGS),
		PDO_FIXED(20000, 3000, PDO_FIXED_FLAGS),
};
const int pd_src_pdo_cnt = ARRAY_SIZE(pd_src_pdo);

const uint32_t pd_snk_pdo[] = {
		PDO_FIXED(5000, 500, PDO_FIXED_FLAGS),
		PDO_BATT(4750, 21000, 15000),
		PDO_VAR(4750, 21000, 3000),
};
const int pd_snk_pdo_cnt = ARRAY_SIZE(pd_snk_pdo);

void pd_set_input_current_limit(int port, uint32_t max_ma,
				uint32_t supply_voltage)
{
	int red = supply_voltage == 20000;
	int green = supply_voltage == 5000;
	int blue = supply_voltage && !(red || green);
	gpio_set_level(GPIO_LED_R_L, !red);
	gpio_set_level(GPIO_LED_G_L, !green);
	gpio_set_level(GPIO_LED_B_L, !blue);
}

int pd_is_valid_input_voltage(int mv)
{
	/* Any voltage less than the max is allowed */
	return 1;
}

void pd_transition_voltage(int idx)
{
}

int pd_set_power_supply_ready(int port)
{
	return EC_SUCCESS; /* we are ready */
}

void pd_power_supply_reset(int port)
{
}

int pd_snk_is_vbus_provided(int port)
{
	/* assume the alert was programmed to detect bus voltage above 4.5V */
	return (gpio_get_level(GPIO_VBUS_ALERT_L) == 0);
}

int pd_board_checks(void)
{
	return EC_SUCCESS;
}

int pd_check_power_swap(int port)
{
	/* Always refuse power swap */
	return 0;
}

int pd_check_data_swap(int port, int data_role)
{
	/* Always allow data swap */
	return 1;
}

void pd_check_pr_role(int port, int pr_role, int flags)
{
}

void pd_check_dr_role(int port, int dr_role, int flags)
{
}

void pd_execute_data_swap(int port, int data_role)
{
	/* Do nothing */
}

/* ----------------- Vendor Defined Messages ------------------ */
const struct svdm_response svdm_rsp = {
	.identity = NULL,
	.svids = NULL,
	.modes = NULL,
};

int pd_custom_vdm(int port, int cnt, uint32_t *payload,
		  uint32_t **rpayload)
{
	return 0;
}

const struct svdm_amode_fx supported_modes[] = {
};
const int supported_modes_cnt = ARRAY_SIZE(supported_modes);

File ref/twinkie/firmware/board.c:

/* Copyright (c) 2014 The Chromium OS Authors. All rights reserved.
 * Use of this source code is governed by a BSD-style license that can be
 * found in the LICENSE file.
 */
/* Twinkie dongle configuration */

#include "adc.h"
#include "adc_chip.h"
#include "common.h"
#include "console.h"
#include "ec_version.h"
#include "gpio.h"
#include "hooks.h"
#include "i2c.h"
#include "ina2xx.h"
#include "printf.h"
#include "registers.h"
#include "system.h"
#include "task.h"
#include "usb_descriptor.h"
#include "util.h"

void cc2_event(enum gpio_signal signal)
{
	ccprintf("INA!\n");
}

void vbus_event(enum gpio_signal signal)
{
	ccprintf("INA!\n");
}

#include "gpio_list.h"

/* Initialize board. */
void board_config_pre_init(void)
{
	/* enable SYSCFG clock */
	STM32_RCC_APB2ENR |= 1 << 0;
	/* Remap USART DMA to match the USART driver and TIM2 DMA */
	STM32_SYSCFG_CFGR1 |= (1 << 9) | (1 << 10) /* Remap USART1 RX/TX DMA */
			   |  (1 << 29);/* Remap TIM2 DMA */
	/* 40 MHz pin speed on UART PA9/PA10 */
	STM32_GPIO_OSPEEDR(GPIO_A) |= 0x003C0000;
	/* 40 MHz pin speed on TX clock out PB9 */
	STM32_GPIO_OSPEEDR(GPIO_B) |= 0x000C0000;
}

static void board_init(void)
{
	/* Enable interrupts for INAs. */
	gpio_enable_interrupt(GPIO_CC2_ALERT_L);
	gpio_enable_interrupt(GPIO_VBUS_ALERT_L);

	/* Calibrate INA0 (VBUS) with 1mA/LSB scale */
	ina2xx_init(0, 0x8000, INA2XX_CALIB_1MA(15 /*mOhm*/));
	/* Disable INA1 (VCONN2) to avoid leaking current */
	ina2xx_init(1, 0, INA2XX_CALIB_1MA(15 /*mOhm*/));
}
DECLARE_HOOK(HOOK_INIT, board_init, HOOK_PRIO_DEFAULT);

/* ADC channels */
const struct adc_t adc_channels[] = {
	/* USB PD CC lines sensing. Converted to mV (3300mV/4096). */
	[ADC_CH_CC1_PD] = {"CC1_PD", 3300, 4096, 0, STM32_AIN(1)},
	[ADC_CH_CC2_PD] = {"CC2_PD", 3300, 4096, 0, STM32_AIN(3)},
};
BUILD_ASSERT(ARRAY_SIZE(adc_channels) == ADC_CH_COUNT);

/* I2C ports */
const struct i2c_port_t i2c_ports[] = {
	{"master", I2C_PORT_MASTER, 100, GPIO_I2C_SCL, GPIO_I2C_SDA},
};
const unsigned int i2c_ports_used = ARRAY_SIZE(i2c_ports);

const void * const usb_strings[] = {
	[USB_STR_DESC] = usb_string_desc,
	[USB_STR_VENDOR] = USB_STRING_DESC("Google Inc."),
	[USB_STR_PRODUCT] = USB_STRING_DESC("Twinkie"),
	[USB_STR_VERSION] = USB_STRING_DESC(CROS_EC_VERSION32),
	[USB_STR_SNIFFER] = USB_STRING_DESC("USB-PD Sniffer"),
	[USB_STR_CONSOLE_NAME] = USB_STRING_DESC("Shell"),
	[USB_STR_COMMAND_NAME] = USB_STRING_DESC("Commands"),
	[USB_STR_SERIALNO] = USB_STRING_DESC(""),
};
BUILD_ASSERT(ARRAY_SIZE(usb_strings) == USB_STR_COUNT);

/* Generate a USB serial number from unique chip ID. */
const char *board_read_serial(void)
{
	static char str[USB_STRING_LEN];

	if (str[0] == '\0') {
		uint8_t *id;
		int pos = 0;
		int idlen = system_get_chip_unique_id(&id);
		int i;

		for (i = 0; i < idlen && pos < sizeof(str); i++, pos += 2)
			snprintf(&str[pos], sizeof(str)-pos, "%02x", id[i]);
	}

	return str;
}

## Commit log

2020-10-14 Reference material: Data sheets, original Twinkie design
2020-10-14 Initial schematics based on Twinkie
2020-11-02 More references
2020-11-02 Half a PCB - USB-C side laid out
2020-11-03 Ratsnest Zero \o/
2020-11-04 Silk screen, ground plane fixes, move vias out of pads, part numbers
2020-11-04 Tact switch datasheet
2020-11-05 Switch uC to combo LQFP+QFN footprint, re-route most connections
2020-11-05 Adapt silkscreen to changed layout
2020-11-06 Name and logos on silkscreen
2020-11-06 v0.9 including fabrication files
2020-11-18 ref: Add F072CB datasheet, switch USB-C plug
2020-11-18 Many reworks based on David's and Vincent's feedback
    * The USB plug wouldn't straddle a 1.6mm board, so switched to
    a different one
    * Redid the USB section to make room for the new plug
    * Twinkie firmware needs some special pin functions I wasn't aware
    of, so some signals had to be moved to different pins
    * Misc other tweaks like merging resistor values
2020-11-18 v0.99 with fabrication files
    * Switch USB-MicroB receptacle to version with drill slots
    * Expand VBUS connections on USB-C plug
2020-12-28 First batch of v1.0 fixes
    * Restore QFN/TQFP combo footprint for U4, make sure it stays
    * Grow some VBUS copper pours
    * Make U4 decap ground connections less solid for better soldering
2020-12-28 Add small shell program to communicate on bulk endpoints in Windows
2020-12-28 Save log of high speed trace impedance calculations
2020-12-28 Add photos of assembled v0.99
2020-12-28 Add relief to J2 cutout corners, update ground connections
2020-12-28 Add I2C pullup resistors
2020-12-28 Improve C2/4/5/6 solderability
2020-12-28 Solderability improvememts around J3
    * Extend J3 pads for easier hand soldering
    * Move FB1, C1 to reach pads better
    * Move J3 closer to board edge
2020-12-28 Round PCB corners
2020-12-28 Bump silkscreen version to 1.0
2020-12-29 Add back bootloader selection via USB_ID
2020-12-29 Improve U4 supply routing
2020-12-29 Switch Gerber output dir to v1.0
2021-02-13 Last minute fixes
    * Add back C8 which had accidentally been deleted
    * Flip Q4 source<->drain
2021-02-13 v1.0 fabrication files
2021-02-16 Fix stupid mistake in shell.py
2021-02-16 Add README and recent photos
2021-02-16 Remove stray gerber zip
2021-02-16 Link to Greg's project
2021-02-17 Temporarily add firmware binary made by Chromium based build
2021-02-20 Add assembly instructions with photos
2021-03-09 Add stripped Twinkie firmware sources with Twonkie support
2021-04-14 hw: Fix ambiguous U4 part numbers
    U4 still had plenty of references to the F042 that was originally
    designed in there, with only the value field indicating the correct
    F072. Update all fields to correctly point to the F072 part.
    Fixes #3.
2021-04-14 Update schematics PDF
2021-04-20 Some README updates after another round of building
2023-02-04 Twonkie v2.0 alpha hardware
    Upgrade the project to KiCad 6.0, fixing a whole bunch of new ERC/DRC
    errors and warnings.
    Switch from INA260 to INA237 which supports EPR voltage ranges, with
    external shunt resistors.
    Strap a previously unused pin on the STM32 to indicate the board
    revision, so firmware can detect which hardware it's running on.
2023-02-04 v2.0: Updates based on David's review
    * Wire sense resistors according to datasheet (measured current flows
    along a long edge instead of diagonally)
    * Rotate R28 and move C9 to allow for that, this also unclutters the
    vias and traces around the INA237 north sides and improves copper
    plane shape
    * Connect inner VBUS shape to upper via group too
2023-02-04 Update USB-C receptacle part
    The EDAC part is obsolete; use a fitting drop-in replacement from GCT.
    Fixes #6.
2023-02-04 Readme updates
    * Switch everything to v2.0
    * Add section about replacement parts (inspired by #6)
    * Add section for electronics noobs (inspired by #5)
2023-06-11 hw: Update AD8606 P/N, change all caps to C_Small symbol
2023-06-11 fw: Remove superfluous check
    Since supported_modes is an array of structs the check always yields true.
    Caused a compiler warning so out it goes.
2023-06-11 fw: Add twonkiev2 board with INA237 support, fix INA260
    * Add 24-bit I2C read support to I2C code
    (and fix endian conversion bug)
    * Update ina2xx driver to use I2C builtin endian conversion
    * Move high-level functions from sniffer code into ina2xx driver
    * Support INA237 command set
    * Fix broken current reading on INA260
2023-06-11 fw: Remove default board, add script to build all boards
2023-06-11 hw: Move TP1 a bit so it doesn't look like a pin 1 marker (ask me how i know)
2023-06-11 README updates
2023-06-11 hw: Re-export BOM, schematic PDF and Gerbers
2023-06-11 More README updates
2023-11-25 Add link to XenGi's 0.8mm PCB fork
    Closes #10
2024-04-27 Fix VCONN INA I2C address in schematic
    Just a typo - board and firmware are fine.
    Fixes #11
2024-07-14 Upgrade to KiCad 8, add missing files
2025-09-19 README.md: Update OSH Park link to v2
